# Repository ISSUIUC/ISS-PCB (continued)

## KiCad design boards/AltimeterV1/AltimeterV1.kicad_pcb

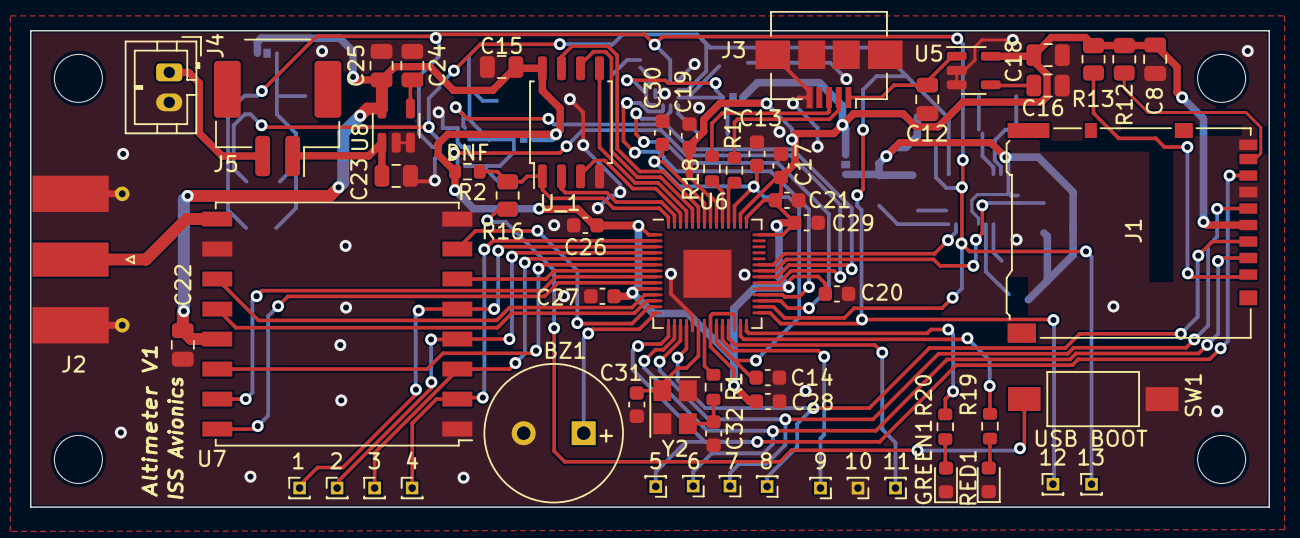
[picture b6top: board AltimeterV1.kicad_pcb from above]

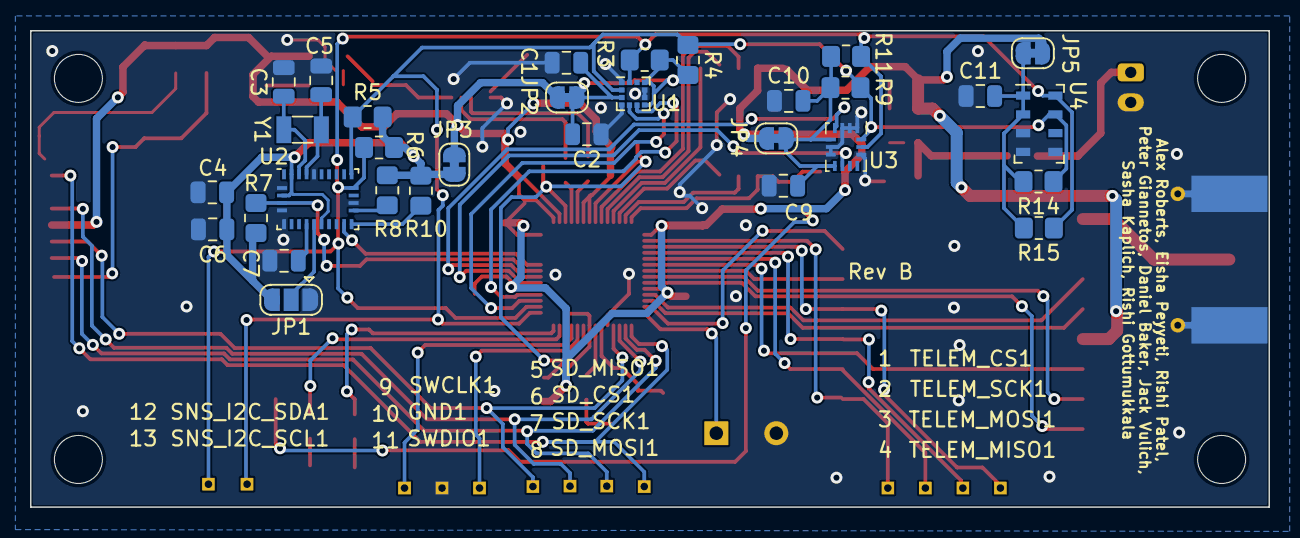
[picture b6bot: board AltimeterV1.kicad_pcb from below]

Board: 2 copper layers, 82.5 x 31.8 mm, 90 parts (31 on the bottom side), 65 nets.

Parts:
BZ1: Buzzer; MagneticBuzzer_PUI_AT-0927-TT-6-R
C1, C2, C9, C10, C11, C15: 100nF; C_0805_2012Metric
C3, C5: 22pF; C_0805_2012Metric
C4, C6, C7: 0.1uF; C_0805_2012Metric
C8: 10u; C_0805_2012Metric
C12, C18, C23, C25: 1uF; C_0805_2012Metric
C13, C17: 1 uF; C_0603_1608Metric
C14, C19, C20, C21, C26, C27, C28, C29, C30: 100 nF; C_0603_1608Metric
C16, C24: 10nF; C_0805_2012Metric
C22: 10uF; C_0805_2012Metric
C31, C32: 30pF; C_0603_1608Metric
GND1: TestPoint; PinHeader_1x01_P1.00mm_Vertical
GREEN1: LED_0603_1608Metric
J1: Micro_SD_Card; microSD_HC_Hirose_DM3AT-SF-PEJM5
J2: Conn_Coaxial; SMA_Molex_73251-1153_EdgeMount_Horizontal
J3: USB_B_Micro; USB_Micro-B_Amphenol_10104110_Horizontal
J4: Conn_01x02_Female; JST_PH_B2B-PH-K_1x02_P2.00mm_Vertical
J5: Molex Micro-Lock 5055780271; Molex_CLIK-Mate_502494-0270_1x02-1MP_P2.00mm_Horizontal
JP1: SolderJumper_3_Open; SolderJumper-3_P1.3mm_Open_RoundedPad1.0x1.5mm
JP2, JP5: Jumper_NC_Small; SolderJumper-2_P1.3mm_Bridged_RoundedPad1.0x1.5mm
JP3, JP4: Jumper_2_Bridged; SolderJumper-2_P1.3mm_Bridged_RoundedPad1.0x1.5mm
R1, R19, R20: 1k; R_0603_1608Metric
R2: DNF; R_0603_1608Metric
R3, R4, R5, R6, R8, R9, R10, R11: 2.2k; R_0805_2012Metric_Pad1.20x1.40mm_HandSolder
R7, R14, R15: 10k; R_0805_2012Metric_Pad1.20x1.40mm_HandSolder
R12, R13: 10k; R_0805_2012Metric
R16: 1k; R_0805_2012Metric
R17, R18: 27; R_0603_1608Metric
RED1: LED_0603_1608Metric
SD_CS1: TestPoint; PinHeader_1x01_P1.00mm_Vertical
SD_MISO1: TestPoint; PinHeader_1x01_P1.00mm_Vertical
SD_MOSI1: TestPoint; PinHeader_1x01_P1.00mm_Vertical
SD_SCK1: TestPoint; PinHeader_1x01_P1.00mm_Vertical
SNS_I2C_SCL1, SNS_I2C_SDA1: TestPoint; PinHeader_1x01_P1.00mm_Vertical
SW1: SW_Push; SW_SPST_FSMSM
SWCLK1: TestPoint; PinHeader_1x01_P1.00mm_Vertical
SWDIO1: TestPoint; PinHeader_1x01_P1.00mm_Vertical
TELEM_CS1: TestPoint; PinHeader_1x01_P1.00mm_Vertical
TELEM_MISO1: TestPoint; PinHeader_1x01_P1.00mm_Vertical
TELEM_MOSI1: TestPoint; PinHeader_1x01_P1.00mm_Vertical
TELEM_SCK1: TestPoint; PinHeader_1x01_P1.00mm_Vertical
U1: KX134-1211; LGA-12_2x2mm_P0.5mm
U2: BNO086; LGA-28_5.2x3.8mm_P0.5mm
U3: LSM6DSLTR; Bosch_LGA-14_3x2.5mm_P0.5mm
U4: MS5611-01BA03; LGA-8_3x5mm_P1.25mm
U5, U8: LD3985M33R_SOT23; SOT-23-5
U6: RP2040; QFN-56-1EP_7x7mm_P0.4mm_EP3.2x3.2mm
U7: RFM96W-433S2; HOPERF_RFM9XW_SMD
U_1: W25Q128JVS; SOIC-8_5.23x5.23mm_P1.27mm
Y1: 32.768kHz; Crystal_SMD_3215-2Pin_3.2x1.5mm
Y2: Crystal_GND24; Crystal_SMD_3225-4Pin_3.2x2.5mm

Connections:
/1V1: C13.1, C14.1, C30.1, U6.23 (DVDD), U6.45 (VREG_VOUT), U6.50 (DVDD)
/3V3: C8.2, C15.1, C17.1, C18.1, C19.1, C20.1, C21.1, C22.1, C25.1, C26.1, C27.1, C28.1, C29.1, J1.4 (VDD), JP2.1 (A), JP3.2 (B), JP4.1 (A), JP5.1 (A), R2.1, R12.1, R13.1, U5.5 (VOUT), U6.1 (IOVDD), U6.10 (IOVDD), U6.22 (IOVDD), U6.26 (RUN), U6.33 (IOVDD), U6.42 (IOVDD), U6.43 (ADC_AVDD), U6.44 (VREG_IN), U6.48 (USB_VDD), U6.49 (IOVDD), U7.13 (3.3V), U8.5 (VOUT), U_1.8 (VCC)
/BNO086_BOOT: R7.1, U2.4 (BOOTN), U6.36 (GPIO24)
/BNO086_INT: U2.14 (H_INTN), U6.37 (GPIO25)
/BNO VDD: C4.1, C6.1, JP1.3 (B), JP3.1 (A), R5.2, R6.2, R7.2, R8.2, R10.2, U2.3 (VDD), U2.11 (NRST), U2.28 (VDDIO)
/KX134_INT1: U1.5 (INT1), U6.31 (GPIO20)
/KX134_INT2: U1.6 (INT2), U6.32 (GPIO21)
/LED_1: R19.1, U6.27 (GPIO16)
/LED_2: R20.1, U6.28 (GPIO17)
/LSM6 VDD: C9.2, C10.2, JP4.2 (B), R9.2, R11.2, U3.5 (VDDIO), U3.8 (VDD)
/LSM6DSLTR_INT1: U3.4 (INT1), U6.35 (GPIO23)
/LSM6DSLTR_INT2: U3.9 (INT2), U6.34 (GPIO22)
/PWM_BUZZ: BZ1.1 (-), U6.14 (GPIO11)
/QSPI_SCLK: U6.52 (QSPI_SCLK), U_1.6 (CLK)
/QSPI_SD0: U6.53 (QSPI_SD0), U_1.5 (DI(IO0))
/QSPI_SD1: U6.55 (QSPI_SD1), U_1.2 (DO(IO1))
/QSPI_SD2: U6.54 (QSPI_SD2), U_1.3 (IO2)
/QSPI_SD3: U6.51 (QSPI_SD3), U_1.7 (IO3)
/QSPI_SS: R2.2, R16.2, U6.56 (QSPI_SS), U_1.1 (~CS)
/SNS_I2C_SCL: R3.1, R6.1, R11.1, R15.1, SNS_I2C_SCL1.1, U1.12 (SCLK/SCL), U2.19 (H_SCL/SCK/RX), U3.13 (SCL), U4.8 (SCLK), U6.30 (GPIO19)
/SNS_I2C_SDA: R4.1, R5.1, R9.1, R14.1, SNS_I2C_SDA1.1, U1.2 (SDI/SDA), U2.20 (H_SDA/H_MISO/TX), U3.14 (SDA), U4.7 (SDI/SDA), U6.29 (GPIO18)
/SPI_SDCARD_CS: J1.2 (DAT3/CD), SD_CS1.1, U6.16 (GPIO13)
/SPI_SDCARD_MISO: J1.7 (DAT0), SD_MISO1.1, U6.15 (GPIO12)
/SPI_SDCARD_MOSI: J1.3 (CMD), SD_MOSI1.1, U6.18 (GPIO15)
/SPI_SDCARD_SCK: J1.5 (CLK), SD_SCK1.1, U6.17 (GPIO14)
/SWCLK: SWCLK1.1, U6.24 (SWCLK)
/SWDIO: SWDIO1.1, U6.25 (SWD)
/SW_CS: R16.1, SW1.2
/TELEM_CS: TELEM_CS1.1, U6.3 (GPIO1), U7.5 (NSS)
/TELEM_GPIO_1: U6.8 (GPIO6), U7.15 (DIO1)
/TELEM_GPIO_2: U6.9 (GPIO7), U7.16 (DIO2)
/TELEM_GPIO_3: U6.11 (GPIO8), U7.11 (DIO3)
/TELEM_GPIO_4: U6.12 (GPIO9), U7.12 (DIO4)
/TELEM_GPIO_5: U6.13 (GPIO10), U7.7 (DIO5)
/TELEM_INT: U6.6 (GPIO4), U7.14 (DIO0)
/TELEM_MISO: TELEM_MISO1.1, U6.2 (GPIO0), U7.2 (MISO)
/TELEM_MOSI: TELEM_MOSI1.1, U6.5 (GPIO3), U7.3 (MOSI)
/TELEM_RST: U6.7 (GPIO5), U7.6 (RESET)
/TELEM_SCK: TELEM_SCK1.1, U6.4 (GPIO2), U7.4 (SCK)
/USB_D+: J3.3 (D+), R18.1
/USB_D-: J3.2 (D-), R17.1
/VBAT: C23.1, J5.1, U8.1 (VIN)
/XIN: C31.2, U6.20 (XIN), Y2.1
/XOUT: R1.2, U6.21 (XOUT)
/XTAL Resistor: C32.2, R1.1, Y2.3
GND: BZ1.2 (+), C1.2, C2.1, C3.2, C4.2, C5.2, C6.2, C7.2, C8.1, C9.1, C10.1, C11.1, C12.2, C13.2, C14.2, C15.2, C16.1, C17.2, C18.2, C19.2, C20.2, C21.2, C22.2, C23.2, C24.1, C25.2, C26.2, C27.2, C28.2, C29.2, C30.2, C31.1, C32.1, GND1.1, GREEN1.1 (K), J1.6 (VSS), J1.9 (SHIELD), J2.2 (Ext), J3.5 (GND), J3.6 (Shield), J4.2, JP1.1 (A), RED1.1 (K), SW1.1, U1.1 (SDO/ADDR), U1.4 (TRIG), U1.8 (GND), U1.9 (GND), U2.2 (GND), U2.5 (PS1), U2.6 (PS0/WAKE), U2.17 (H_SA0_MOSI), U2.25 (GNDIO), U3.1 (SDO/SA0), U3.2 (SDX), U3.3 (SCX), U3.6 (GND), U3.7 (GND), U3.12 (CS), U4.3 (GND), U4.4 (CSB), U4.5 (CSB), U5.2 (GND), U5.3 (INH), U6.19 (TESTEN), U6.57 (GND), U7.1 (GND), U7.8 (GND), U7.10 (GND), U8.2 (GND), U8.3 (INH), U_1.4 (GND), Y2.2, Y2.4
unnamed: C1.1, C2.2, JP2.2 (B), R3.2, R4.2, U1.3 (VDDIO), U1.7 (VDD), U1.10 (nCS)
unnamed: C3.1, U2.27 (XIN32), Y1.1
unnamed: C5.1, U2.26 (XOUT32/CLKSEL1), Y1.2
unnamed: C7.1, U2.9 (CAP)
unnamed: C11.2, JP5.2 (B), R14.2, R15.2, U4.1 (VDD), U4.2 (PS)
unnamed: C12.1, J3.1 (VBUS), U5.1 (VIN)
unnamed: C16.2, U5.4 (BYP)
unnamed: C24.2, U8.4 (BYP)
unnamed: GREEN1.2 (A), R20.2
unnamed: J1.1 (DAT2), R13.2
unnamed: J1.8 (DAT1), R12.2
unnamed: J2.1 (In), U7.9 (ANT)
unnamed: J4.1, J5.2
unnamed: JP1.2 (C), U2.10 (CLKSEL0)
unnamed: R8.1, U2.16 (ENV_SDA)
unnamed: R10.1, U2.15 (ENV_SCL)
unnamed: R17.2, U6.46 (USB_DM)
unnamed: R18.2, U6.47 (USB_DP)
unnamed: R19.2, RED1.2 (A)

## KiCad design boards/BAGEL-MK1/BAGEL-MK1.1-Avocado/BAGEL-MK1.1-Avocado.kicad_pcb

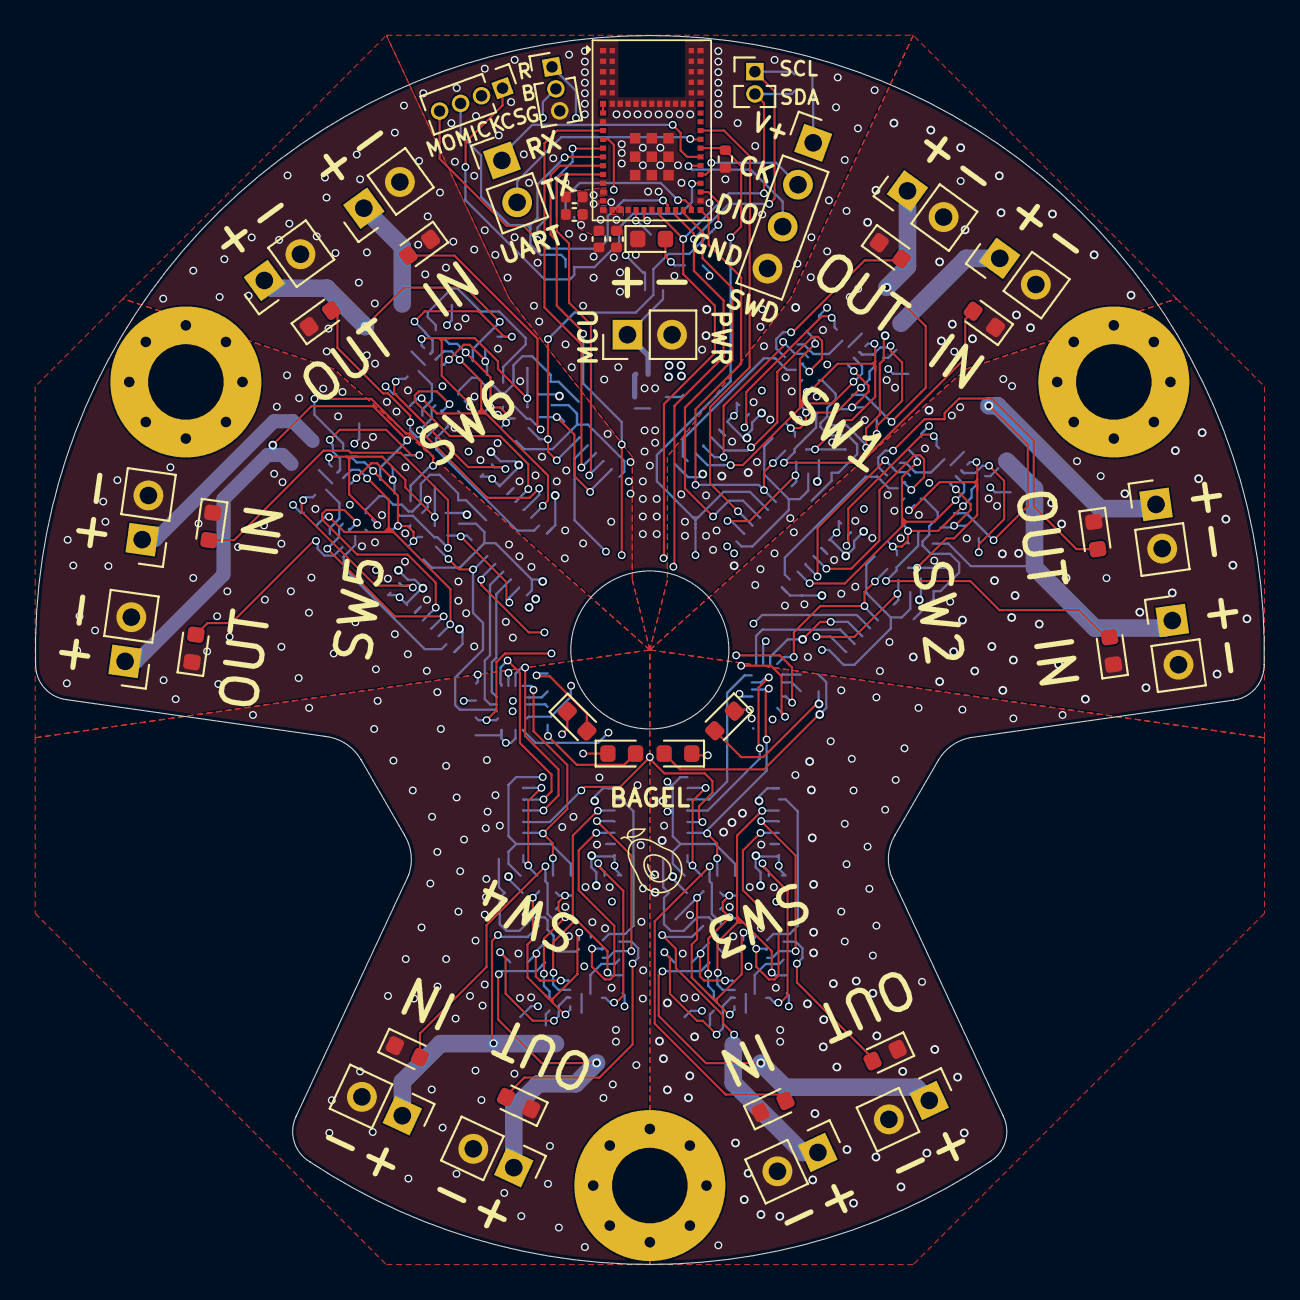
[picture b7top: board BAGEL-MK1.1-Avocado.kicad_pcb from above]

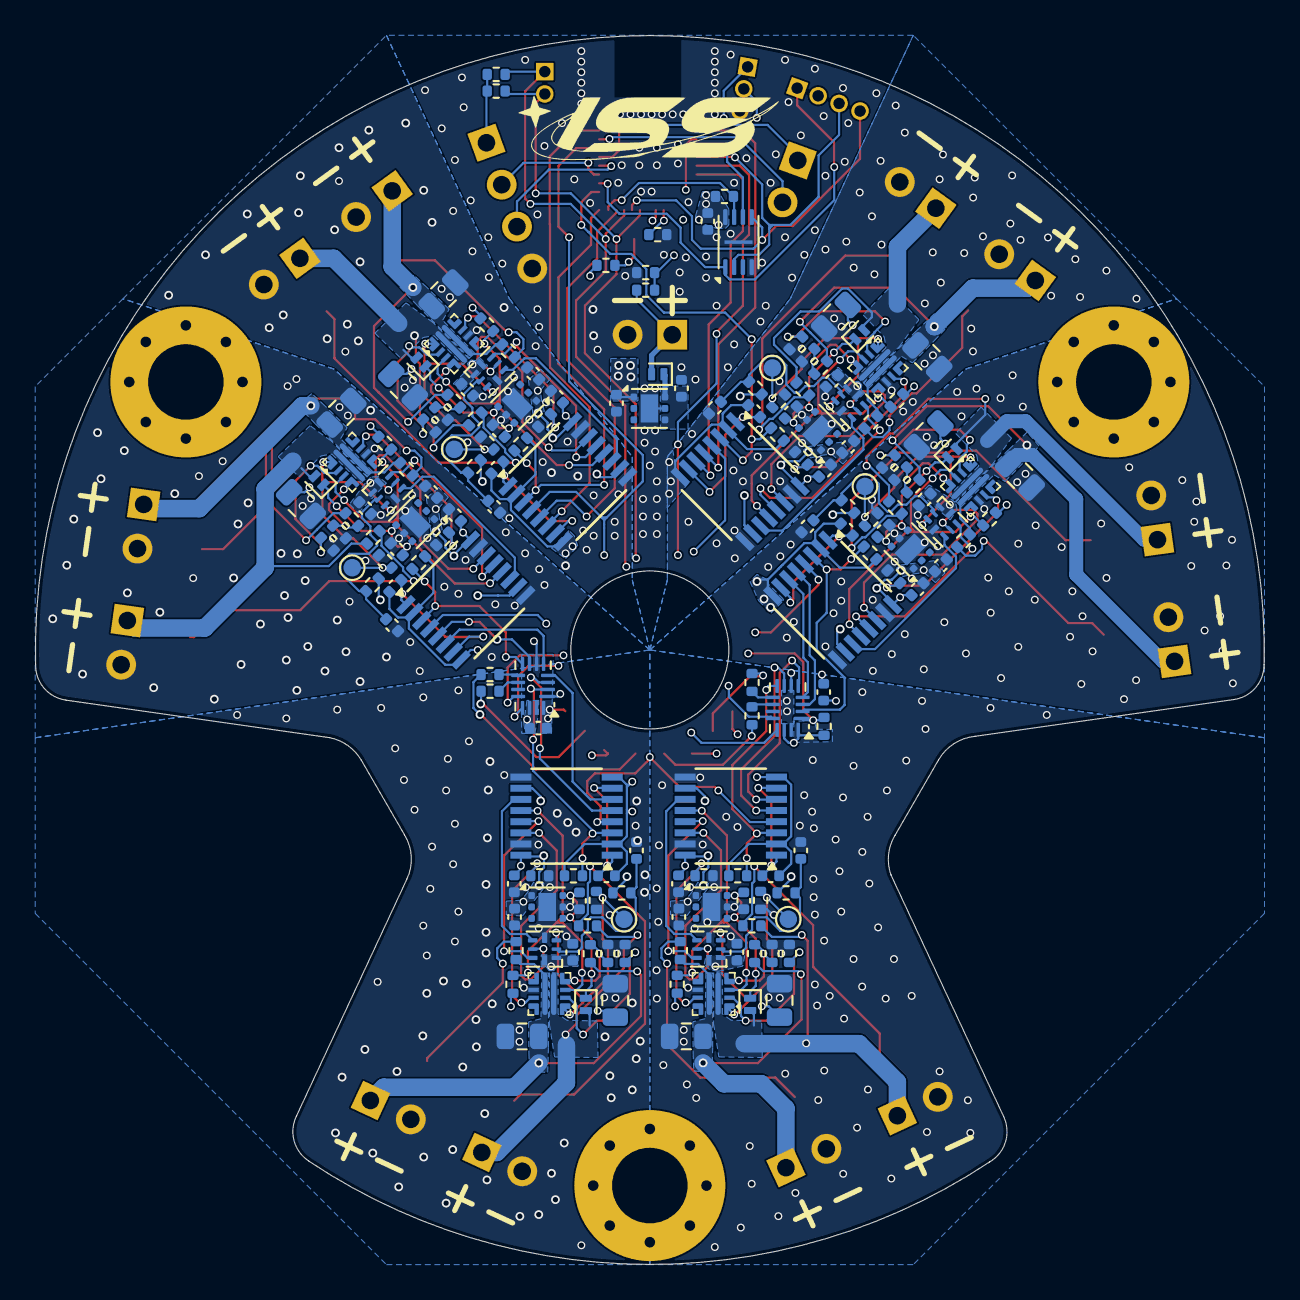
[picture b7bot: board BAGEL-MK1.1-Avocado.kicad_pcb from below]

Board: 4 copper layers, 70.0 x 70.0 mm, 210 parts (166 on the bottom side), 144 nets.

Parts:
C101, C103, C104, C105, C108, C109, C201, C202, C203, C207, C301, C302, C303, C307, C401, C402, C403, C407, C501, C502, C503, C507, C601, C602, C603, C607, C701, C702, C703, C707: 100nF; C_0402_1005Metric
C102: 4.7uF; C_0402_1005Metric
C106, C204, C304, C404, C504, C604, C704: 1uF; C_0402_1005Metric
C107, C205, C305, C405, C505, C605, C705: 2.2uF; C_0402_1005Metric
C206, C306, C406, C506, C606, C706: 100uF; C_0805_2012Metric
C208, C308, C408, C508, C608, C708: 22uF; C_0805_2012Metric
D101, D201, D301, D401, D501, D601, D701: SDM05U40CSP-7; D_SOD-882
D102, D103, D202, D302, D402, D502, D602, D702: RED; LED_0603_1608Metric
D104: ORANGE; LED_0603_1608Metric
D105, D203, D303, D403, D503, D603, D703: GREEN; LED_0603_1608Metric
D106: BLUE; LED_0603_1608Metric
H101, H102, H103: MountingHole_Pad; MountingHole_4.3mm_M4_Pad_Via
J101, J102, J103, J104, J105, J106, J109, J110, J113, J114, J115, J116, J117, J118: Conn_01x02; PinHeader_1x02_P2.54mm_Vertical
J107: Conn_01x03; PinHeader_1x03_P1.27mm_Vertical
J108: Conn_01x04; PinHeader_1x04_P2.54mm_Vertical
J111: Conn_01x02; PinHeader_1x02_P1.27mm_Vertical
J112: Conn_01x04; PinHeader_1x04_P1.27mm_Vertical
J201, J301, J401, J501, J601, J701: Conn_01x01; TestPoint_Pad_D1.0mm
R101, R102, R103, R113, R201, R202, R204, R205, R301, R302, R304, R305, R401, R402, R404, R405, R501, R502, R504, R505, R601, R602, R604, R605, R701, R702, R704, R705: 10k; R_0402_1005Metric
R104, R105, R106, R107, R108, R109, R112, R203, R303, R403, R503, R603, R703: 4.7k; R_0402_1005Metric
R110, R111: 100k; R_0402_1005Metric
R206, R306, R406, R506, R606, R706: 680; R_0402_1005Metric
R207, R307, R407, R507, R607, R707: 390k; R_0402_1005Metric
R208, R308, R408, R508, R608, R708: 300k; R_0402_1005Metric
R209, R309, R409, R509, R609, R709: 500k; R_0402_1005Metric
R210, R310, R410, R510, R610, R710: 1k; R_0402_1005Metric
U101: W25Q16JLUX; Winbond_USON-8-1EP_3x2mm_P0.5mm_EP0.2x1.6mm
U102: STM32WB1MMC; LGA77_6P5X10_STM
U103, U203, U303, U403, U503, U603, U703: TPS7A25; WSON-6-1EP_2x2mm_P0.65mm_EP1x1.6mm
U104, U105: TCAL9538; UQFN-16_1.8x2.6mm_P0.4mm
U201, U301, U401, U501, U601, U701: ISO7742; SSOP-16_3.9x4.9mm_P0.635mm
U202, U302, U402, U502, U602, U702: SN74AUP1G74RSER; UQFN-RSE0008A
U204, U304, U404, U504, U604, U704: TPS25947; VQFN-HR-RPW0010A

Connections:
/BLUE_LED: R108.1, U105.10 (P7)
/BOOT: J107.2, R102.2, U102.22 (BOOT0)
/EXP_RESET: R103.1, U102.13 (PA2), U104.1 (~RESET), U105.1 (~RESET)
/FLASH_CS: J112.1, U101.1 (~CS), U102.33 (PB4)
/FLASH_RESET: R101.2, U101.7 (~HOLD/~RESET/IO_{3}), U102.29 (PA7)
/GPIO_Clock: R113.2, U102.37 (PA0), U201.4 (INB), U301.4 (INB), U401.4 (INB), U501.4 (INB), U601.4 (INB), U701.4 (INB)
/GREEN_LED: R107.1, U105.9 (P6)
/I2C_SCL: J111.1, R112.1, U102.27 (PB6), U104.12 (SCL), U105.12 (SCL)
/I2C_SDA: J111.2, R109.1, U102.25 (PB7), U104.13 (SDA), U105.13 (SDA)
/MainBatt_V: D101.2 (A), J109.1, R110.2
/NRST: J107.1, U102.23 (NRST)
/ORANGE_LED: R106.1, U104.10 (P7)
/PG_ISO_1: U102.28 (PA3), U201.5 (OUTC)
/PG_ISO_2: U104.7 (P4), U301.5 (OUTC)
/PG_ISO_3: U104.3 (P1), U401.5 (OUTC)
/PG_ISO_4: U105.7 (P4), U501.5 (OUTC)
/PG_ISO_5: U105.3 (P1), U601.5 (OUTC)
/PG_ISO_6: U102.9 (PA4), U701.5 (OUTC)
/RED_LED: R105.1, U104.9 (P6)
/SPI_MISO: J112.3, U101.2 (DO/IO_{1}), U102.12 (PA6)
/SPI_MOSI: J112.4, U101.5 (DI/IO_{0}), U102.26 (PB5)
/SPI_SCK: J112.2, U101.6 (CLK), U102.11 (PA1)
/SWCLK: J108.2, U102.34 (PA14)
/SWDIO: J108.3, U102.35 (PA13)
/SubBatt_GND1: C201.2, C203.2, C204.2, C205.2, C206.2, C207.1, C208.2, D202.1 (K), D203.1 (K), J101.2, J102.2, R202.1, R206.1, R207.2, R209.2, U201.9 (GND2), U201.15 (GND2), U202.4 (GND), U203.5 (GND), U203.7 (Thermal), U204.8 (GND)
/SubBatt_GND2: C301.2, C303.2, C304.2, C305.2, C306.2, C307.1, C308.2, D302.1 (K), D303.1 (K), J103.2, J104.2, R302.1, R306.1, R307.2, R309.2, U301.9 (GND2), U301.15 (GND2), U302.4 (GND), U303.5 (GND), U303.7 (Thermal), U304.8 (GND)
/SubBatt_GND3: C401.2, C403.2, C404.2, C405.2, C406.2, C407.1, C408.2, D402.1 (K), D403.1 (K), J105.2, J106.2, R402.1, R406.1, R407.2, R409.2, U401.9 (GND2), U401.15 (GND2), U402.4 (GND), U403.5 (GND), U403.7 (Thermal), U404.8 (GND)
/SubBatt_GND4: C501.2, C503.2, C504.2, C505.2, C506.2, C507.1, C508.2, D502.1 (K), D503.1 (K), J113.2, J114.2, R502.1, R506.1, R507.2, R509.2, U501.9 (GND2), U501.15 (GND2), U502.4 (GND), U503.5 (GND), U503.7 (Thermal), U504.8 (GND)
/SubBatt_GND5: C601.2, C603.2, C604.2, C605.2, C606.2, C607.1, C608.2, D602.1 (K), D603.1 (K), J115.2, J116.2, R602.1, R606.1, R607.2, R609.2, U601.9 (GND2), U601.15 (GND2), U602.4 (GND), U603.5 (GND), U603.7 (Thermal), U604.8 (GND)
/SubBatt_GND6: C701.2, C703.2, C704.2, C705.2, C706.2, C707.1, C708.2, D702.1 (K), D703.1 (K), J117.2, J118.2, R702.1, R706.1, R707.2, R709.2, U701.9 (GND2), U701.15 (GND2), U702.4 (GND), U703.5 (GND), U703.7 (Thermal), U704.8 (GND)
/SubBatt_V1: D201.2 (A), J101.1, R203.1, U204.5 (IN)
/SubBatt_V2: D301.2 (A), J103.1, R303.1, U304.5 (IN)
/SubBatt_V3: D401.2 (A), J105.1, R403.1, U404.5 (IN)
/SubBatt_V4: D501.2 (A), J113.1, R503.1, U504.5 (IN)
/SubBatt_V5: D601.2 (A), J115.1, R603.1, U604.5 (IN)
/SubBatt_V6: D701.2 (A), J117.1, R703.1, U704.5 (IN)
/Switch 1/PG: R205.2, U201.12 (INC), U204.3 (PG/AUXOFF)
/Switch 1/Q: J201.1, R202.2, U202.3 (Q), U204.1 (EN/UVLO)
/Switch 1/Reg_V: C201.1, C203.1, C205.1, C206.1, R204.1, R205.1, U201.10 (EN2), U201.16 (VCC2), U202.1 (~PRE), U202.8 (VCC), U203.1 (VOUT)
/Switch 1/~CLR: C207.2, R204.2, U202.2 (~CLR)
/Switch 1/~Q: U201.11 (IND), U202.5 (~Q)
/Switch 2/PG: R305.2, U301.12 (INC), U304.3 (PG/AUXOFF)
/Switch 2/Q: J301.1, R302.2, U302.3 (Q), U304.1 (EN/UVLO)
/Switch 2/Reg_V: C301.1, C303.1, C305.1, C306.1, R304.1, R305.1, U301.10 (EN2), U301.16 (VCC2), U302.1 (~PRE), U302.8 (VCC), U303.1 (VOUT)
/Switch 2/~CLR: C307.2, R304.2, U302.2 (~CLR)
/Switch 2/~Q: U301.11 (IND), U302.5 (~Q)
/Switch 3/PG: R405.2, U401.12 (INC), U404.3 (PG/AUXOFF)
/Switch 3/Q: J401.1, R402.2, U402.3 (Q), U404.1 (EN/UVLO)
/Switch 3/Reg_V: C401.1, C403.1, C405.1, C406.1, R404.1, R405.1, U401.10 (EN2), U401.16 (VCC2), U402.1 (~PRE), U402.8 (VCC), U403.1 (VOUT)
/Switch 3/~CLR: C407.2, R404.2, U402.2 (~CLR)
/Switch 3/~Q: U401.11 (IND), U402.5 (~Q)
/Switch 4/PG: R505.2, U501.12 (INC), U504.3 (PG/AUXOFF)
/Switch 4/Q: J501.1, R502.2, U502.3 (Q), U504.1 (EN/UVLO)
/Switch 4/Reg_V: C501.1, C503.1, C505.1, C506.1, R504.1, R505.1, U501.10 (EN2), U501.16 (VCC2), U502.1 (~PRE), U502.8 (VCC), U503.1 (VOUT)
/Switch 4/~CLR: C507.2, R504.2, U502.2 (~CLR)
/Switch 4/~Q: U501.11 (IND), U502.5 (~Q)
/Switch 5/PG: R605.2, U601.12 (INC), U604.3 (PG/AUXOFF)
/Switch 5/Q: J601.1, R602.2, U602.3 (Q), U604.1 (EN/UVLO)
/Switch 5/Reg_V: C601.1, C603.1, C605.1, C606.1, R604.1, R605.1, U601.10 (EN2), U601.16 (VCC2), U602.1 (~PRE), U602.8 (VCC), U603.1 (VOUT)
/Switch 5/~CLR: C607.2, R604.2, U602.2 (~CLR)
/Switch 5/~Q: U601.11 (IND), U602.5 (~Q)
/Switch 6/PG: R705.2, U701.12 (INC), U704.3 (PG/AUXOFF)
/Switch 6/Q: J701.1, R702.2, U702.3 (Q), U704.1 (EN/UVLO)
/Switch 6/Reg_V: C701.1, C703.1, C705.1, C706.1, R704.1, R705.1, U701.10 (EN2), U701.16 (VCC2), U702.1 (~PRE), U702.8 (VCC), U703.1 (VOUT)
/Switch 6/~CLR: C707.2, R704.2, U702.2 (~CLR)
/Switch 6/~Q: U701.11 (IND), U702.5 (~Q)
/Switch_1: R201.1, U102.30 (PA12), U201.3 (INA)
/Switch_2: R301.1, U104.8 (P5), U301.3 (INA)
/Switch_3: R401.1, U104.2 (P0), U401.3 (INA)
/Switch_4: R501.1, U105.8 (P5), U501.3 (INA)
/Switch_5: R601.1, U105.2 (P0), U601.3 (INA)
/Switch_6: R701.1, U102.32 (PA11), U701.3 (INA)
/UART_RX: J110.1, U102.36 (PA10)
/UART_TX: J110.2, U102.38 (PA9)
/V_SENSE: R110.1, R111.2, U102.10 (PA8)
/V_out_1: C208.1, J102.1, R208.1, R210.1, U204.6 (OUT)
/V_out_2: C308.1, J104.1, R308.1, R310.1, U304.6 (OUT)
/V_out_3: C408.1, J106.1, R408.1, R410.1, U404.6 (OUT)
/V_out_4: C508.1, J114.1, R508.1, R510.1, U504.6 (OUT)
/V_out_5: C608.1, J116.1, R608.1, R610.1, U604.6 (OUT)
/V_out_6: C708.1, J118.1, R708.1, R710.1, U704.6 (OUT)
/~Q_ISO_1: U102.39 (PA5), U201.6 (OUTD)
/~Q_ISO_2: U104.5 (P3), U301.6 (OUTD)
/~Q_ISO_3: U104.4 (P2), U401.6 (OUTD)
/~Q_ISO_4: U105.5 (P3), U501.6 (OUTD)
/~Q_ISO_5: U105.4 (P2), U601.6 (OUTD)
/~Q_ISO_6: U102.14 (PB8), U701.6 (OUTD)
MCU_GND: C101.2, C102.2, C103.2, C104.2, C105.2, C106.2, C107.2, C108.2, C109.2, C202.2, C302.2, C402.2, C502.2, C602.2, C702.2, D102.1 (K), D103.1 (K), D104.1 (K), D105.1 (K), D106.1 (K), J107.3, J108.4, J109.2, R102.1, R111.1, R113.1, R201.2, R301.2, R401.2, R501.2, R601.2, R701.2, U101.4 (GND), U101.9 (EP), U102.1 (VSS), U102.2 (VSS), U102.3 (VSS), U102.4 (VSS), U102.5 (VSSRF), U102.8 (VSSRF), U102.15 (VSS), U102.17 (VSS), U102.19 (VSS), U102.21 (VSSSMPS), U102.24 (VSS), U102.31 (VSS), U102.43 (VSS), U102.44 (VSS), U102.45 (VSS), U102.46 (VSS), U102.47 (VSS), U102.48 (VSS), U102.49 (VSS), U102.50 (VSS), U102.51 (VSS), U102.52 (VSS), U102.53 (VSS), U102.54 (VSS), U102.55 (VSS), U102.56 (VSS), U102.57 (VSS), U102.58 (VSS), U102.59 (VSS), U102.60 (VSS), U102.61 (VSS), U102.62 (VSS), U102.63 (VSS), U102.64 (VSS), U102.65 (VSS), U102.66 (VSS), U102.67 (VSS), U102.68 (VSS), U102.69 (VSS), U102.70 (VSS), U102.71 (VSS), U102.72 (VSS), U102.73 (VSS), U102.74 (VSS), U102.75 (VSS), U102.76 (VSS), U102.77 (VSS), U103.5 (GND), U103.7 (Thermal), U104.6 (GND), U104.16 (A1), U105.6 (GND), U105.15 (A0), U201.2 (GND1), U201.8 (GND1), U301.2 (GND1), U301.8 (GND1), U401.2 (GND1), U401.8 (GND1), U501.2 (GND1), U501.8 (GND1), U601.2 (GND1), U601.8 (GND1), U701.2 (GND1), U701.8 (GND1)
MCU_V: C101.1, C102.1, C103.1, C104.1, C105.1, C107.1, C108.1, C109.1, C202.1, C302.1, C402.1, C502.1, C602.1, C702.1, J108.1, R101.1, R103.2, R104.2, R109.2, R112.2, U101.8 (VCC), U102.16 (VDDA), U102.18 (VBAT), U102.20 (VDDSMPS), U103.1 (VOUT), U104.14 (VCC), U104.15 (A0), U105.14 (VCC), U105.16 (A1), U201.1 (VCC1), U201.7 (EN1), U301.1 (VCC1), U301.7 (EN1), U401.1 (VCC1), U401.7 (EN1), U501.1 (VCC1), U501.7 (EN1), U601.1 (VCC1), U601.7 (EN1), U701.1 (VCC1), U701.7 (EN1)
unnamed: C106.1, D101.1 (K), U103.4 (EN), U103.6 (VIN)
unnamed: D102.2 (A), R104.1
unnamed: D103.2 (A), R105.2
unnamed: D104.2 (A), R106.2
unnamed: D105.2 (A), R107.2
unnamed: D106.2 (A), R108.2
unnamed: C204.1, D201.1 (K), U203.4 (EN), U203.6 (VIN)
unnamed: D202.2 (A), R203.2
unnamed: D203.2 (A), R210.2
unnamed: C304.1, D301.1 (K), U303.4 (EN), U303.6 (VIN)
unnamed: D302.2 (A), R303.2
unnamed: D303.2 (A), R310.2
unnamed: C404.1, D401.1 (K), U403.4 (EN), U403.6 (VIN)
unnamed: D402.2 (A), R403.2
unnamed: D403.2 (A), R410.2
unnamed: C504.1, D501.1 (K), U503.4 (EN), U503.6 (VIN)
unnamed: D502.2 (A), R503.2
unnamed: D503.2 (A), R510.2
unnamed: C604.1, D601.1 (K), U603.4 (EN), U603.6 (VIN)
unnamed: D602.2 (A), R603.2
unnamed: D603.2 (A), R610.2
unnamed: C704.1, D701.1 (K), U703.4 (EN), U703.6 (VIN)
unnamed: D702.2 (A), R703.2
unnamed: D703.2 (A), R710.2
unnamed: U102.6 (ANT_IN), U102.7 (ANT_OUT)
unnamed: U201.14 (OUTA), U202.6 (D)
unnamed: U201.13 (OUTB), U202.7 (CLK)
unnamed: R206.2, U204.9 (ILM)
unnamed: R207.1, U204.2 (OVLO/OVCSEL)
unnamed: R208.2, R209.1, U204.4 (PGTH/NFLT)
unnamed: U301.14 (OUTA), U302.6 (D)
unnamed: U301.13 (OUTB), U302.7 (CLK)
unnamed: R306.2, U304.9 (ILM)
unnamed: R307.1, U304.2 (OVLO/OVCSEL)
unnamed: R308.2, R309.1, U304.4 (PGTH/NFLT)
unnamed: U401.14 (OUTA), U402.6 (D)
unnamed: U401.13 (OUTB), U402.7 (CLK)
unnamed: R406.2, U404.9 (ILM)
unnamed: R407.1, U404.2 (OVLO/OVCSEL)
unnamed: R408.2, R409.1, U404.4 (PGTH/NFLT)
unnamed: U501.14 (OUTA), U502.6 (D)
unnamed: U501.13 (OUTB), U502.7 (CLK)
unnamed: R506.2, U504.9 (ILM)
unnamed: R507.1, U504.2 (OVLO/OVCSEL)
unnamed: R508.2, R509.1, U504.4 (PGTH/NFLT)
unnamed: U601.14 (OUTA), U602.6 (D)
unnamed: U601.13 (OUTB), U602.7 (CLK)
unnamed: R606.2, U604.9 (ILM)
unnamed: R607.1, U604.2 (OVLO/OVCSEL)
unnamed: R608.2, R609.1, U604.4 (PGTH/NFLT)
unnamed: U701.14 (OUTA), U702.6 (D)
unnamed: U701.13 (OUTB), U702.7 (CLK)
unnamed: R706.2, U704.9 (ILM)
unnamed: R707.1, U704.2 (OVLO/OVCSEL)
unnamed: R708.2, R709.1, U704.4 (PGTH/NFLT)
